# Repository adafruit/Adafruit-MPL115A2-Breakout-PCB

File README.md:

## Adafruit MPL115A2 Breakout PCB

<a href="http://www.adafruit.com/products/992"><br/>
Click here to purchase one from the Adafruit shop
</a>

PCB files for the Adafruit MPL115A2 Breakout. Format is EagleCAD schematic and board layout
* https://www.adafruit.com/product/992

### DESCRIPTION
This pressure sensor from Freescale is a great low-cost sensing solution for measuring barometric pressure. At 1.5 hPa resolution, it's not as precise as our favorite pressure sensor, the BMx280 series, which has up to 0.03 hPa resolution so we don't suggest it as a precision altimeter. However, it's great for basic barometric pressure sensing. The sensor is soldered onto a PCB with 10K pull-up resistors on the I2C pins.

This chip is good for use with power and logic voltages ranging from 2.4V to 5.5V so you can use it with your 3V or 5V microcontroller. There's a basic temperature sensor inside but there's no specifications in the datasheet so we're not sure how accurate it is.

This chip looks and sounds a whole lot like the MPL3115A2 but this is the less precise version, best for barometric sensing only

Using the sensor is easy. For example, if you're using an Arduino, simply connect the VDD pin to the 5V voltage pin, GND to ground, SCL to I2C Clock (Analog 5 on an UNO) and SDA to I2C Data (Analog 4 on an UNO). Then download our MPL115A2 Arduino library and example code for temperature, pressure and basic altitude calculation. Install the library, and load the example sketch. Immediately you'll have the temperature, pressure and altitude data printed in the serial console.

### License

Adafruit invests time and resources providing this open source design, please support Adafruit and open-source hardware by purchasing products from [Adafruit.com](https://www.adafruit.com)!

Creative Commons Attribution, Share-Alike license, check license.txt for more information All text above must be included in any redistribution - 
See license.txt for more information.

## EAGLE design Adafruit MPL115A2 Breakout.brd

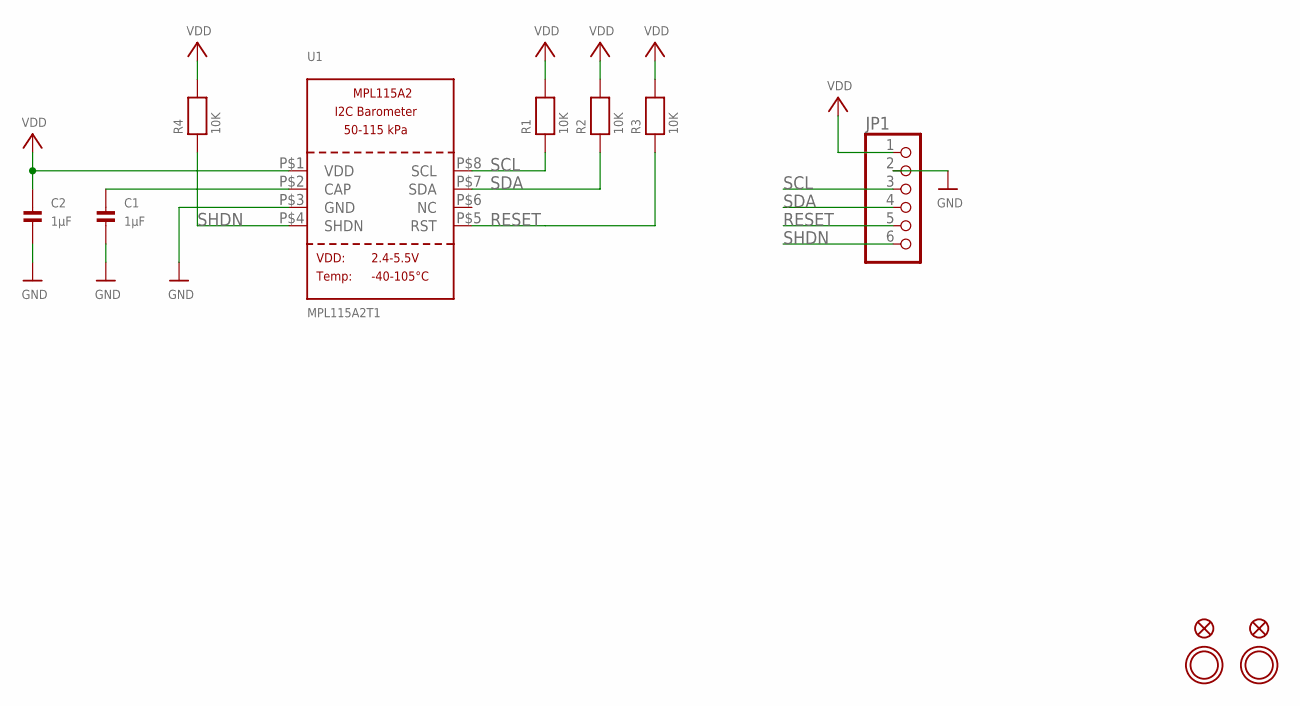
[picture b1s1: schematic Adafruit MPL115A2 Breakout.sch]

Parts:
C1, C2: 1µF; 0805
FID1, FID2: FIDUCIAL""; FIDUCIAL_1MM
JP1: HEADER-1X670MIL; 1X06_ROUND_70
R1, R2, R3, R4: 10K; 0805
U1: MPL115A2T1; LGA8
U$8, U$9: MOUNTINGHOLE2.5; MOUNTINGHOLE_2.5_PLATED

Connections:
GND: C1.2, C2.2, JP1.2, U1.P$3 (GND)
unnamed: C1.1, U1.P$2 (CAP)
RESET: JP1.5, R3.1, U1.P$5 (RST)
SCL: JP1.3, R1.1, U1.P$8 (SCL)
SDA: JP1.4, R2.1, U1.P$7 (SDA)
SHDN: JP1.6, R4.1, U1.P$4 (SHDN)
VDD: C2.1, JP1.1, R1.2, R2.2, R3.2, R4.2, U1.P$1 (VDD)

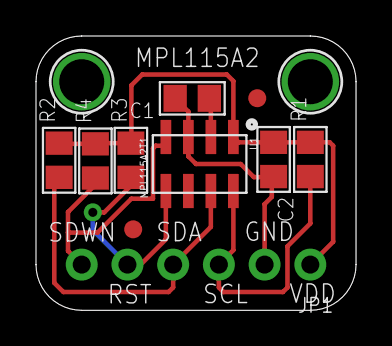
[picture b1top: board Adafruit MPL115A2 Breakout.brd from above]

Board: 2 copper layers, 17.8 x 15.2 mm, 13 parts (1 on the bottom side), 7 nets.

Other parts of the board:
U$14: ADAFRUIT_3.5MM

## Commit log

2016-10-05 init
